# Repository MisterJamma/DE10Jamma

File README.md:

# DE10Jamma

JAMMA/NeoGeo MVS audio, video & control IO for DE10-Nano.

[https://github.com/MisterJamma/DE10Jamma](https://github.com/MisterJamma/DE10Jamma)

Discussion thread: [https://www.atari-forum.com/viewtopic.php?f=120&t=38793](https://www.atari-forum.com/viewtopic.php?f=120&t=38793)

## Description

### Overview
DE10Jamma allows a DE10-Nano board to be connected directly to an arcade cabinet as simply as possible. USB and HDMI serial interfaces are not used, in order to remain as close as possible to the original arcade hardware and avoid unnecessary cost or complexity.

Pull-down resistors on AUDIO_L and AUDIO_R pins allow this board to be detected and coexist with other MiSTer hardware using common rbf files for the cores. See [this commit](https://github.com/MisterJamma/Arcade-GnG_MiSTer/commit/6c7786a7f790a5277f337f6b245e99f6ca4c25ff).

##### Future Developments
Future developments in RTL and software to more fully support DE10Jamma

1. Allow player controls to be used in the OSD.

### Inputs
Inputs are [RC filtered](https://wiki.neogeodev.org/index.php?title=CRE401) to give EMI protection to the FPGA.

No multiplexing, polling or debouncing of the inputs ensures **zero** additional latency & jitter. Cabinet switches are presented to arcade cores exactly as they would be on a real arcade PCB. Arcade cores will include necessary debouncing either in replicated hardware of the original PCB, or in software running on that hardware. When buttons are passed to the ARM host CPU for controlling the UI & selecting arcade cores, the inputs should debounced appropriately in hardware or software.

### Audio Output
2 pole RC filters convert PWM output from DE10-Nano to analog signal. Mono/Stereo jumper JP1 allows stereo signal for MVS wired cabinets, or mono signal for JAMMA wired cabinets. With no jumper fitted, there will be no audio output for the left channel.

2 channel power amplifier drives the speaker loads.

### Video Output
Composite sync is generated by DE10-Nano.

Three 6bit R-2R DACs convert the digital output from DE10-Nano to analog RGB. A single 2R value used in parallel to generate the R value with tighter tolerance. Part-to-part tolerance is typically significantly better than absolute part tolerance, so using a single 2R value for all resistors in the DAC should improve linearity.

No additional latency or incompatibility from HDMI logic and low quality HDMI converters. Resistive DACs are commonly used on arcade PCBs, and allow the original odd resolutions & refresh rates to be supported correctly. Output level is not noticeably lower than a NeoGeo MVS, and well within adjustment range on arcade monitors.

### DC Power Output
DC power output is provided for the DE10-Nano. This should be connected using a short [2.1mm male-male cable](https://www.google.com/search?q=2.1mm+male+to+male&tbm=isch), such as used to connect guitar effects pedals to a power supply.

Arcade power supplies are typically adjustable. DE10-Nano has regulation for lower voltage supplies, and should operate correctly from nominal +5v settings. If +5v rail is adjusted too high, the DE10-Nano's over-voltage protection circuitry will not allow the board to power up.

## Parts List
Qty | Reference(s)         | Value          | Part Number
----|----------------------|----------------|------------
30  | C1, C2, C3, C4, C13, C14, C15, C16, C17, C18, C19, C20, C21, C22, C23, C24, C25, C26, C27, C28, C29, C30, C31, C32, C33, C34, C35, C36, C37, C38 | 10nF | C83170
4   | C5, C6, C7, C11      | 470nF          | C106843
4   | C8, C9, C10, C12     | 1000uF         | C442834
1   | J1, J2, J6           | Long 0.1" pins | C51353
1   | JP1, J3, J4, J5, J11 | 0.1" pins      | C358690
1   | J9                   | 2.5mm JST pins | C160365
1   | J7                   | 0.1" socket    | C35165
1   | J10                  | 2.1mm power    | C319099
1   | R1                   | 100R           | C105577
28  | R2, R3, R34, R35, R36, R37, R38, R39, R40, R41, R42, R43, R44, R45, R60, R61, R62, R63, R64, R65, R66, R67, R68, R69, R70, R71, R72, R73 | 1k | C140870
16  | R4, R100, R101, R102, R103, R104, R105, R106, R107, R108, R109, R110, R111, R112, R113, R114 | 604R | Bourns CAY16-6040F4LF
1   | R8                   | 300k           | C114530
1   | RV1                  | 50k            | C81264
1   | U1                   | TDA7496        | TDA7496
1   | FAN                  | 40mm fan 5/12v | 

###### Notes
   1. Part numbers from [LSSC](https://lcsc.com/) are provided where possible. Values for some components do not match the schematic, and have been adjusted to reduce the number of different components.

   1. J1, J2 and J6 should be inserted into PCB from above, using DE10-Nano to set correct depth. Solder carefully from above & trim to length. Pins should protrude approximately 0.25" from the PCB

   1. J9 is only required for cabinets with 2.5mm pitch JST kick harness connector. It may also be possible to use 0.1" pitch J11 connector with existing kick harness, as the difference in pitch is minimal for a 10way connector.

   1. A 20mm deep fan running on a lower voltage is recommended for reduced noise.

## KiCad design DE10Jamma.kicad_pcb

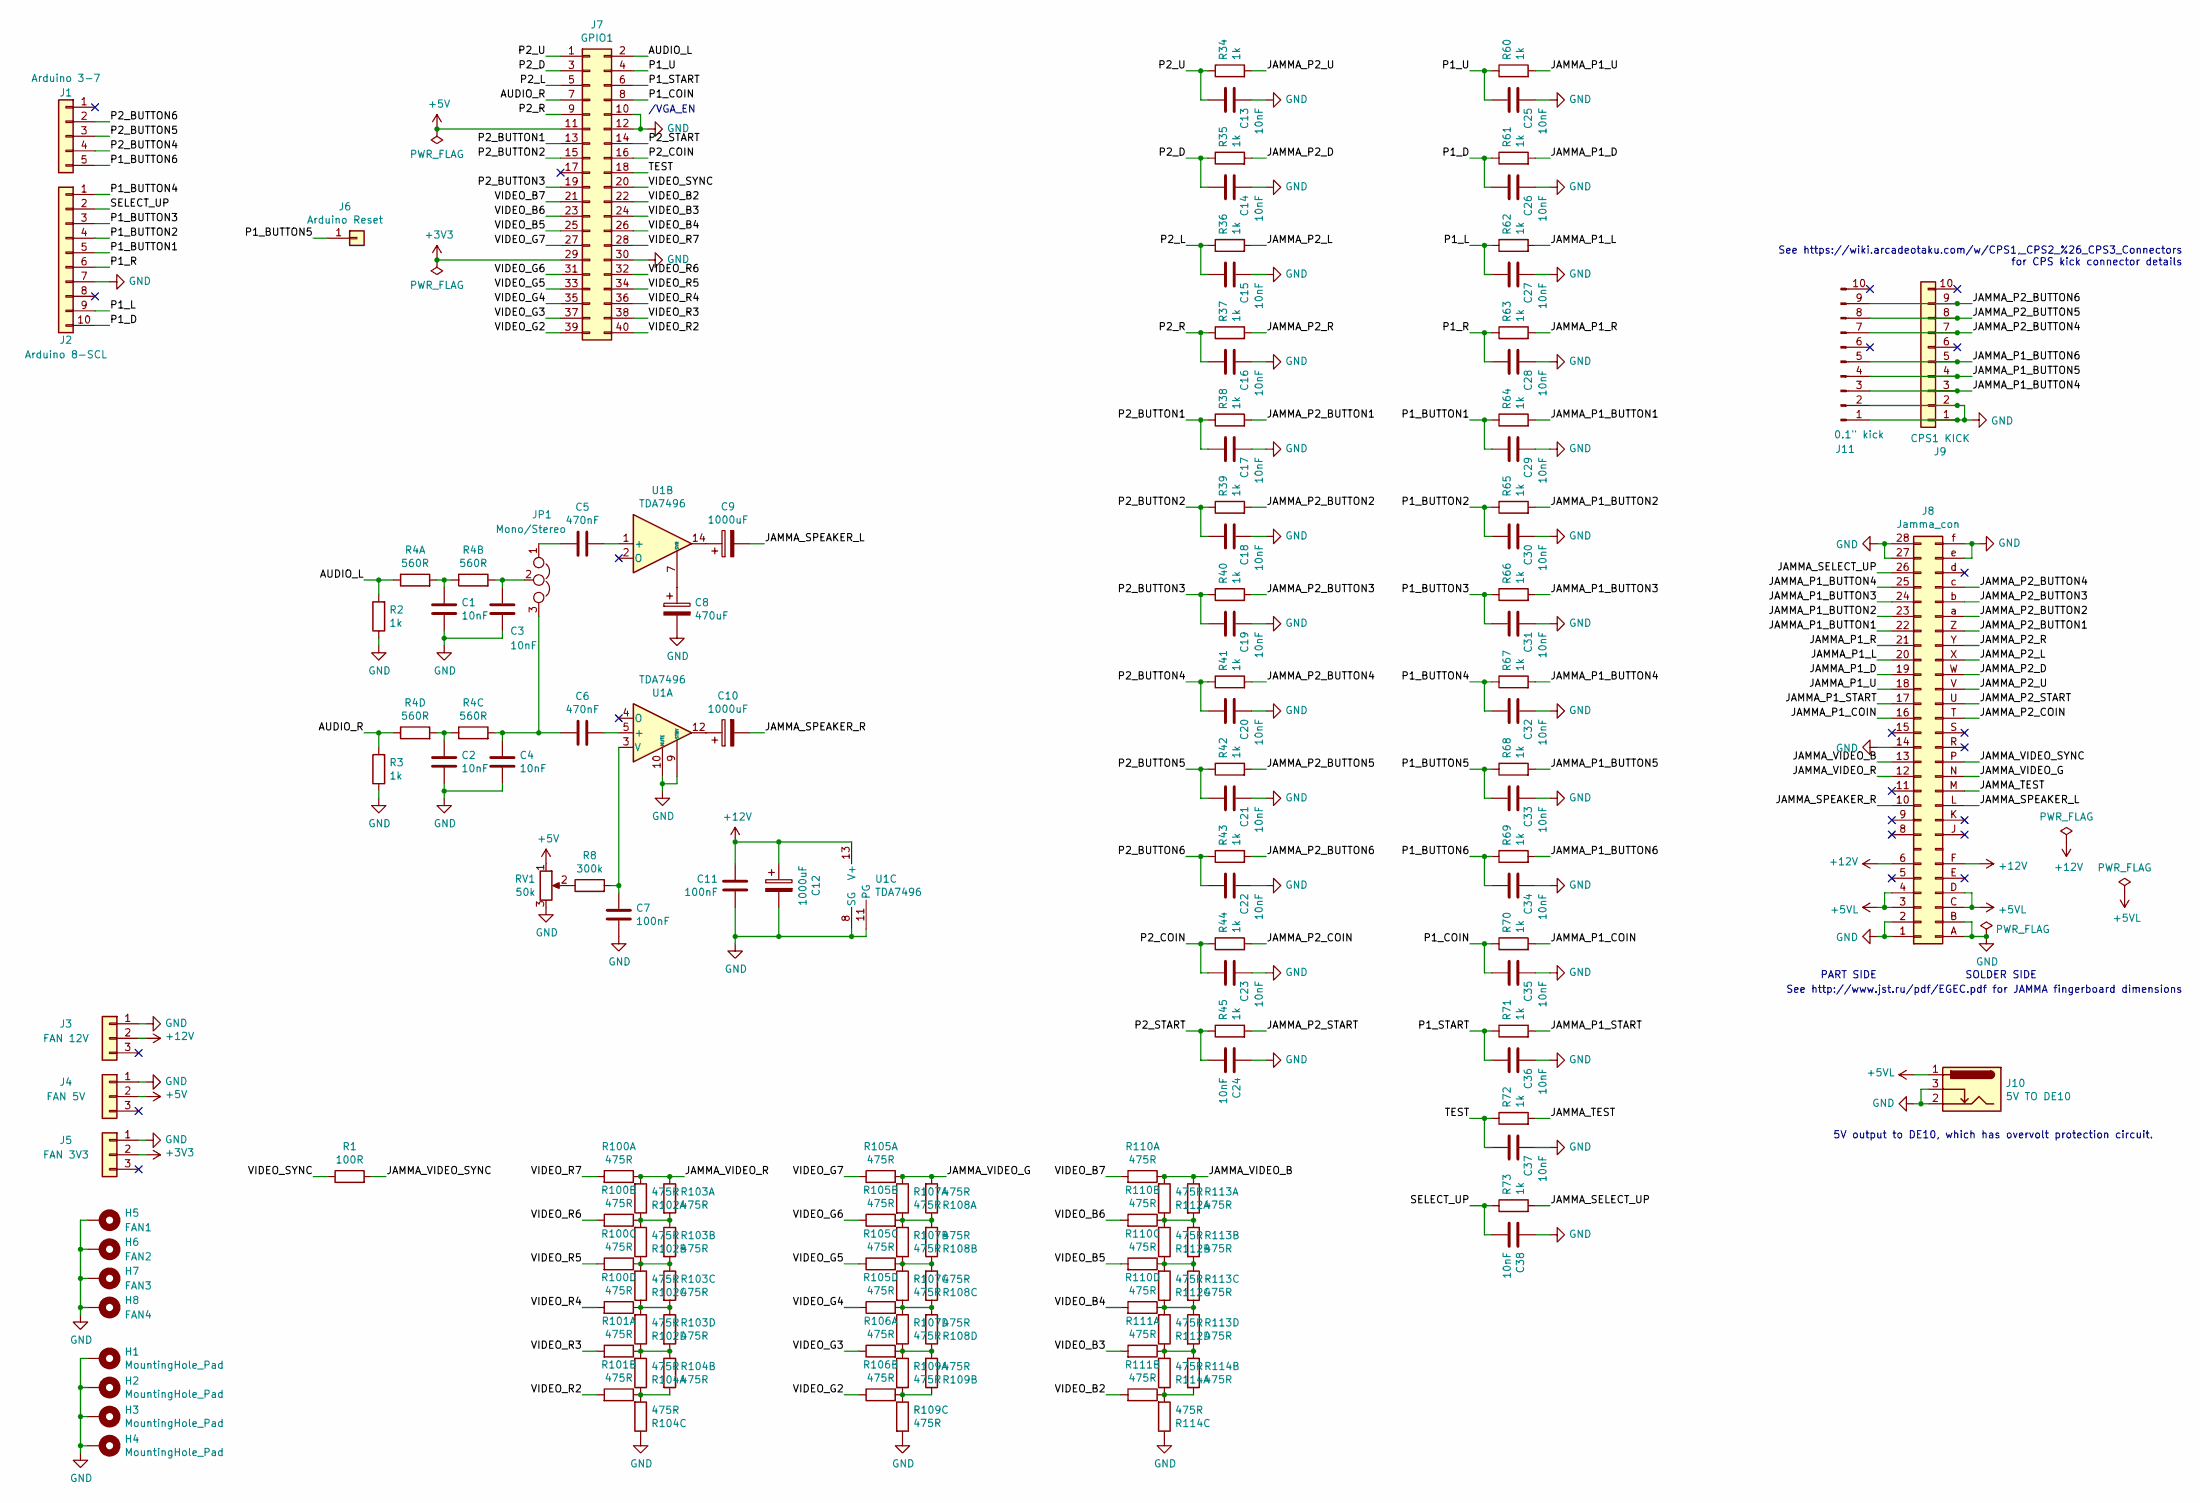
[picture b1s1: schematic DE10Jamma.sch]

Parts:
C1, C2, C3, C4, C13, C14, C15, C16, C17, C18, C19, C20, C21, C22, C23, C24, C25, C26, C27, C28, C29, C30, C31, C32, C33, C34, C35, C36, C37, C38: 10nF; C_0805_2012Metric
C5, C6: 470nF; C_0805_2012Metric
C7, C11: 100nF; C_0805_2012Metric
C8: 470uF; CP_Radial_D10.0mm_P5.00mm
C9, C10, C12: 1000uF; CP_Radial_D10.0mm_P5.00mm
H1, H2, H3, H4: MountingHole_Pad; MountingHole_3mm_Pad_Via
H5: FAN1; MountingHole_3mm
H6: FAN2; MountingHole_3mm
H7: FAN3; MountingHole_3mm
H8: FAN4; MountingHole_3mm
J1: Arduino 3-7; PinHeader_1x05_P2.54mm_Vertical
J2: Arduino 8-SCL; PinHeader_1x10_P2.54mm_Vertical
J3: FAN 12V; PinHeader_1x03_P2.54mm_Vertical
J4: FAN 5V; PinHeader_1x03_P2.54mm_Vertical
J5: FAN 3V3; PinHeader_1x03_P2.54mm_Vertical
J6: Arduino Reset; PinHeader_1x01_P2.54mm_Vertical
J7: GPIO1; PinSocket_2x20_P2.54mm_Vertical
J8: Jamma_con; JAMMA-56
J9: CPS1 KICK; JST_EH_B10B-EH-A_1x10_P2.50mm_Vertical
J10: 5V TO DE10; BarrelJack_Horizontal
J11: 0.1\" kick; PinHeader_1x10_P2.54mm_Vertical
JP1: Mono/Stereo; PinHeader_1x03_P2.54mm_Vertical
R1: 100R; C_0805_2012Metric
R2, R3, R34, R35, R36, R37, R38, R39, R40, R41, R42, R43, R44, R45, R60, R61, R62, R63, R64, R65, R66, R67, R68, R69, R70, R71, R72, R73: 1k; C_0805_2012Metric
R4: 560R; R_Array_Convex_4x0603
R8: 300k; C_0805_2012Metric
R100, R101, R102, R103, R104, R105, R106, R107, R108, R109, R110, R111, R112, R113, R114: 475R; R_Array_Convex_4x0603
RV1: 50k; Potentiometer_Vishay_T73YP_Vertical
U1: TDA7496; TO-220-15_P2.54x2.54mm_StaggerOdd_Lead4.58mm_Vertical

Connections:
+3V3: J5.2, J7.29
+5V: J4.2, J7.11, RV1.1
+5VL: J8.3 (+5V), J8.4 (+5V), J8.C (+5V), J8.D (+5V), J10.1
+12V: C11.1, C12.1, J3.2, J8.6 (+12V), J8.F (+12V), U1.13 (V+)
/AUDIO_L: J7.2, R2.2, R4.8
/AUDIO_R: J7.7, R3.2, R4.5
/JAMMA_P1_BUTTON1: J8.22 (P1_BUTTON_1), R64.2
/JAMMA_P1_BUTTON2: J8.23 (P1_BUTTON_2), R65.2
/JAMMA_P1_BUTTON3: J8.24 (P1_BUTTON_3), R66.2
/JAMMA_P1_BUTTON4: J8.25 (P1_BUTTON_4), J9.3, J11.3, R67.2
/JAMMA_P1_BUTTON5: J9.4, J11.4, R68.2
/JAMMA_P1_BUTTON6: J9.5, J11.5, R69.2
/JAMMA_P1_COIN: J8.16 (COIN_1), R70.2
/JAMMA_P1_D: J8.19 (P1_DOWN), R61.2
/JAMMA_P1_L: J8.20 (P1_LEFT), R62.2
/JAMMA_P1_R: J8.21 (P1_RIGHT), R63.2
/JAMMA_P1_START: J8.17 (START_1), R71.2
/JAMMA_P1_U: J8.18 (P1_UP), R60.2
/JAMMA_P2_BUTTON1: J8.Z (P2_BUTTON_1), R38.2
/JAMMA_P2_BUTTON2: J8.a (P2_BUTTON_2), R39.2
/JAMMA_P2_BUTTON3: J8.b (P2_BUTTON_3), R40.2
/JAMMA_P2_BUTTON4: J8.c (P2_BUTTON_4), J9.7, J11.7, R41.2
/JAMMA_P2_BUTTON5: J9.8, J11.8, R42.2
/JAMMA_P2_BUTTON6: J9.9, J11.9, R43.2
/JAMMA_P2_COIN: J8.T (COIN_2), R44.2
/JAMMA_P2_D: J8.W (P2_DOWN), R35.2
/JAMMA_P2_L: J8.X (P2_LEFT), R36.2
/JAMMA_P2_R: J8.Y (P2_RIGHT), R37.2
/JAMMA_P2_START: J8.U (START_2), R45.2
/JAMMA_P2_U: J8.V (P2_UP), R34.2
/JAMMA_SELECT_UP: J8.26 (SELECT_UP), R73.2
/JAMMA_SPEAKER_L: C9.2, J8.L (SPEAKER-)
/JAMMA_SPEAKER_R: C10.2, J8.10 (SPEAKER+)
/JAMMA_TEST: J8.M (TEST), R72.2
/JAMMA_VIDEO_B: J8.13 (VIDEO_BLUE), R110.8, R112.1, R113.8
/JAMMA_VIDEO_G: J8.N (VIDEO_GREEN), R105.1, R107.8, R108.1
/JAMMA_VIDEO_R: J8.12 (VIDEO_RED), R100.8, R102.1, R103.8
/JAMMA_VIDEO_SYNC: J8.P (VIDEO_SYNC), R1.2
/P1_BUTTON1: C29.2, J2.5, R64.1
/P1_BUTTON2: C30.2, J2.4, R65.1
/P1_BUTTON3: C31.2, J2.3, R66.1
/P1_BUTTON4: C32.2, J2.1, R67.1
/P1_BUTTON5: C33.2, J6.1, R68.1
/P1_BUTTON6: C34.2, J1.5, R69.1
/P1_COIN: C35.2, J7.8, R70.1
/P1_D: C26.2, J2.10, R61.1
/P1_L: C27.2, J2.9, R62.1
/P1_R: C28.2, J2.6, R63.1
/P1_START: C36.2, J7.6, R71.1
/P1_U: C25.2, J7.4, R60.1
/P2_BUTTON1: C17.2, J7.13, R38.1
/P2_BUTTON2: C18.2, J7.15, R39.1
/P2_BUTTON3: C19.2, J7.19, R40.1
/P2_BUTTON4: C20.2, J1.4, R41.1
/P2_BUTTON5: C21.2, J1.3, R42.1
/P2_BUTTON6: C22.2, J1.2, R43.1
/P2_COIN: C23.2, J7.16, R44.1
/P2_D: C14.2, J7.3, R35.1
/P2_L: C15.2, J7.5, R36.1
/P2_R: C16.2, J7.9, R37.1
/P2_START: C24.2, J7.14, R45.1
/P2_U: C13.2, J7.1, R34.1
/SELECT_UP: C38.2, J2.2, R73.1
/TEST: C37.2, J7.18, R72.1
/VIDEO_B2: J7.22, R111.2
/VIDEO_B3: J7.24, R111.1
/VIDEO_B4: J7.26, R110.4
/VIDEO_B5: J7.25, R110.3
/VIDEO_B6: J7.23, R110.2
/VIDEO_B7: J7.21, R110.1
/VIDEO_G2: J7.39, R106.7
/VIDEO_G3: J7.37, R106.8
/VIDEO_G4: J7.35, R105.5
/VIDEO_G5: J7.33, R105.6
/VIDEO_G6: J7.31, R105.7
/VIDEO_G7: J7.27, R105.8
/VIDEO_R2: J7.40, R101.2
/VIDEO_R3: J7.38, R101.1
/VIDEO_R4: J7.36, R100.4
/VIDEO_R5: J7.34, R100.3
/VIDEO_R6: J7.32, R100.2
/VIDEO_R7: J7.28, R100.1
/VIDEO_SYNC: J7.20, R1.1
GND: C1.2, C2.2, C3.2, C4.2, C7.2, C8.2, C11.2, C12.2, C13.1, C14.1, C15.1, C16.1, C17.1, C18.1, C19.1, C20.1, C21.1, C22.1, C23.1, C24.1, C25.1, C26.1, C27.1, C28.1, C29.1, C30.1, C31.1, C32.1, C33.1, C34.1, C35.1, C36.1, C37.1, C38.1, H1.1, H2.1, H3.1, H4.1, H5.1, H6.1, H7.1, H8.1, J2.7, J3.1, J4.1, J5.1, J7.10, J7.12, J7.30, J8.1 (GND), J8.2 (GND), J8.14 (VIDEO_GND), J8.27 (GND), J8.28 (GND), J8.A (GND), J8.B (GND), J8.e (GND), J8.f (GND), J9.1, J9.2, J10.2, J10.3, J11.1, J11.2, R2.1, R3.1, R104.6, R109.3, R114.6, RV1.3, U1.8 (SG), U1.9 (STBY), U1.10 (MUTE), U1.11 (PG), U1.15 (PG)
unnamed: C1.1, R4.1, R4.7
unnamed: C2.1, R4.4, R4.6
unnamed: C3.1, JP1.2, R4.2
unnamed: C4.1, C6.1, JP1.3, R4.3
unnamed: C5.1, JP1.1
unnamed: C5.2, U1.1 (+)
unnamed: C6.2, U1.5 (+)
unnamed: C7.1, R8.2, U1.3 (V)
unnamed: C8.1, U1.7 (SVR)
unnamed: C9.1, U1.14
unnamed: C10.1, U1.12
unnamed: R8.1, RV1.2
unnamed: R100.5, R102.4, R102.6, R103.3, R103.5
unnamed: R100.6, R102.3, R102.7, R103.2, R103.6
unnamed: R100.7, R102.2, R102.8, R103.1, R103.7
unnamed: R101.7, R104.2, R104.3, R104.8
unnamed: R101.8, R102.5, R103.4, R104.1, R104.7
unnamed: R105.2, R107.1, R107.7, R108.2, R108.8
unnamed: R105.3, R107.2, R107.6, R108.3, R108.7
unnamed: R105.4, R107.3, R107.5, R108.4, R108.6
unnamed: R106.1, R107.4, R108.5, R109.2, R109.8
unnamed: R106.2, R109.1, R109.6, R109.7
unnamed: R110.5, R112.4, R112.6, R113.3, R113.5
unnamed: R110.6, R112.3, R112.7, R113.2, R113.6
unnamed: R110.7, R112.2, R112.8, R113.1, R113.7
unnamed: R111.7, R114.2, R114.3, R114.8
unnamed: R111.8, R112.5, R113.4, R114.1, R114.7

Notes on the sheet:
PART SIDE
SOLDER SIDE
/VGA_EN
5V output to DE10, which has overvolt protection circuit.
See http://www.jst.ru/pdf/EGEC.pdf for JAMMA fingerboard dimensions
See https://wiki.arcadeotaku.com/w/CPS1,_CPS2_%26_CPS3_Connectors for CPS kick connector details

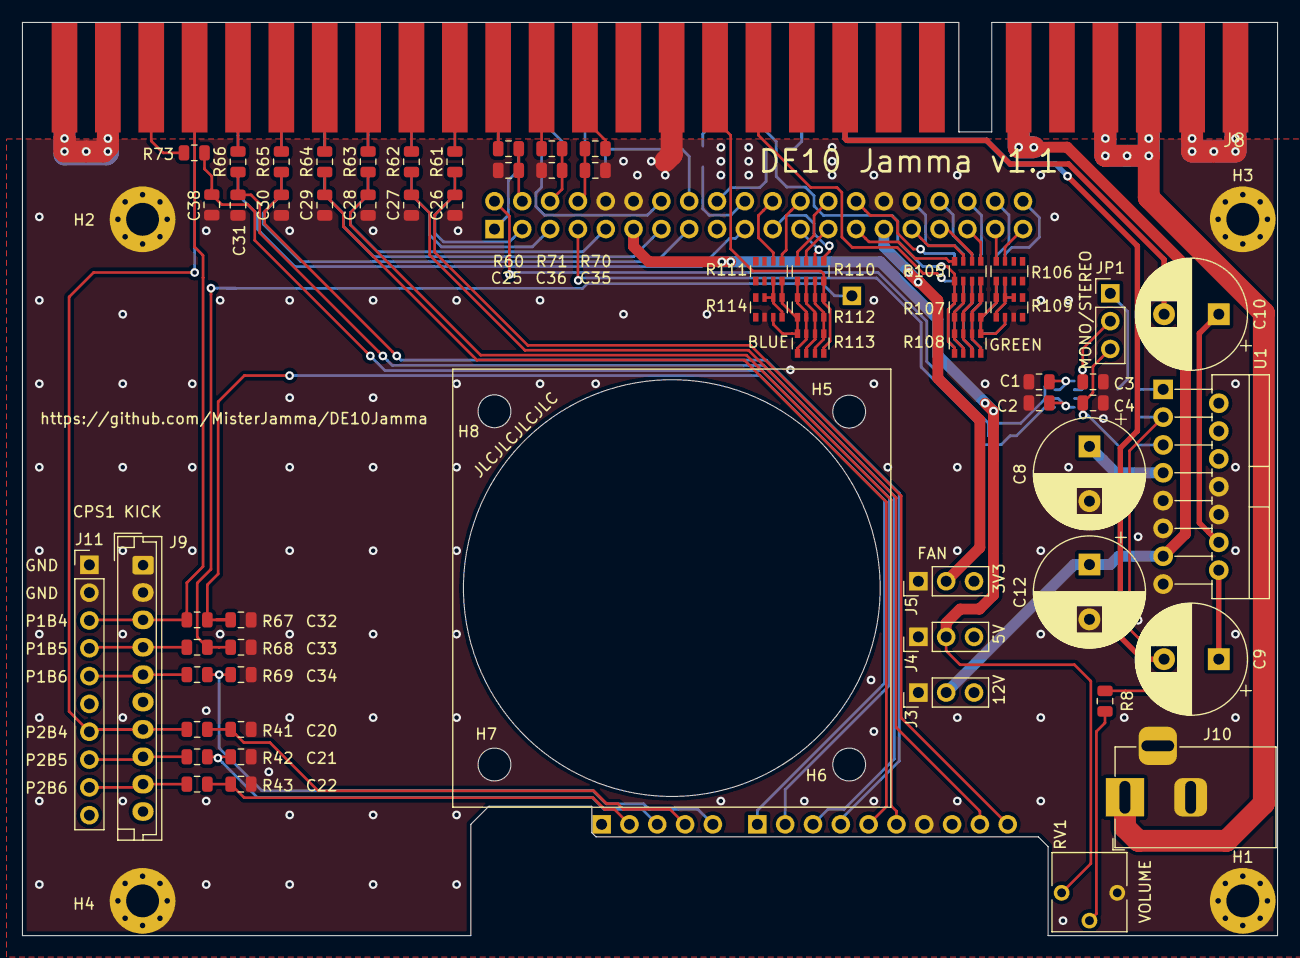
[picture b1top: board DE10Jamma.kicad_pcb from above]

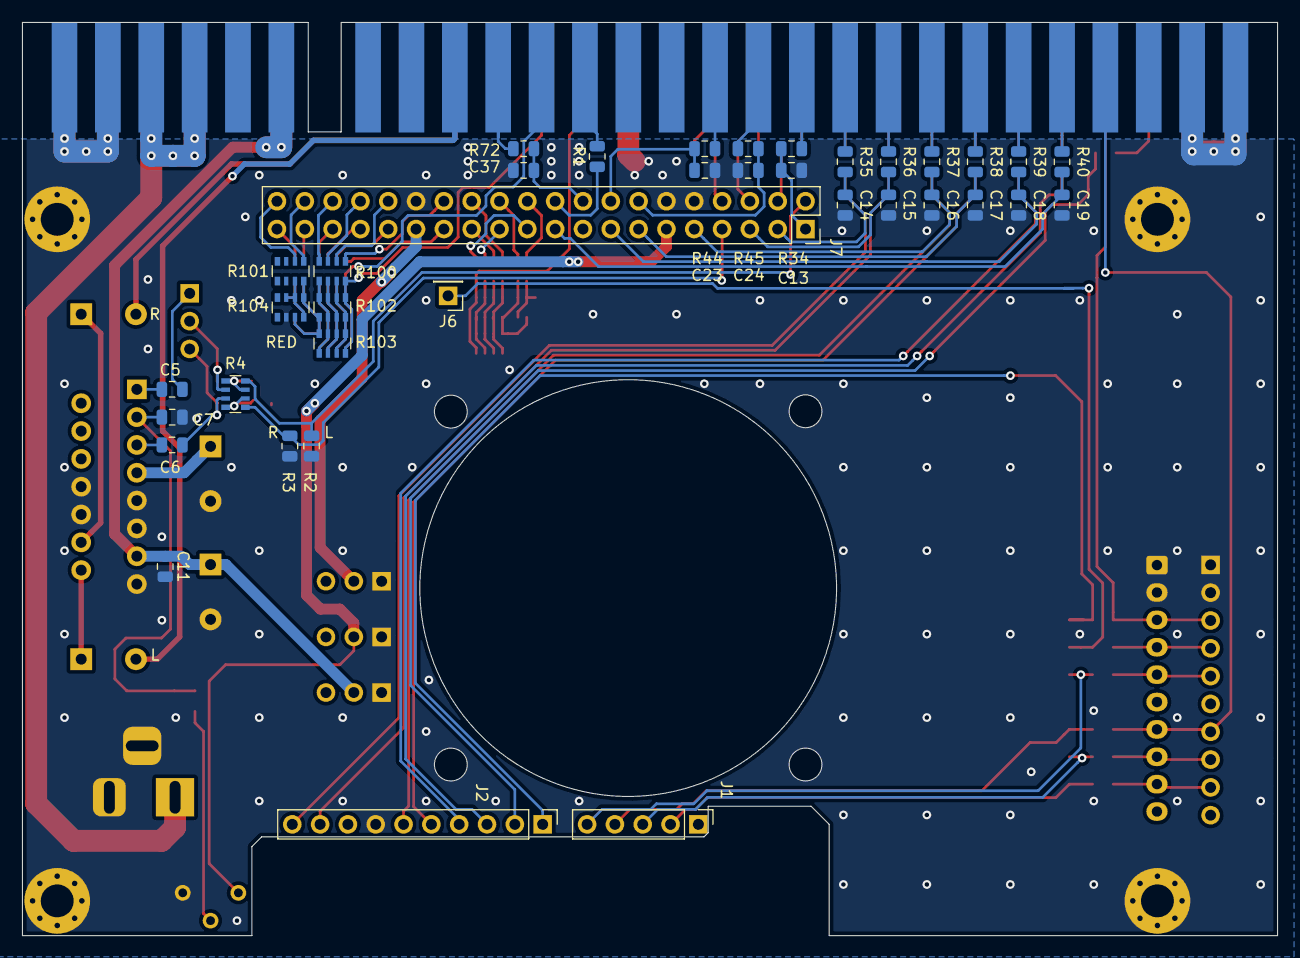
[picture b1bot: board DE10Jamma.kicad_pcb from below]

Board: 2 copper layers, 114.6 x 83.4 mm, 106 parts (37 on the bottom side), 111 nets.

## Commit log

2020-05-03 pdf of schematic
2020-07-05 clean before sending to manufacture
2020-07-05 Add mono/stereo jumper. Remove out of date pdf
2020-08-02 Use smaller footprint for r-packs. Rework mono/stereo jumper to avoid potential DC path issues if inputs have DC offset. General routing & silk screen cleanup.
2020-08-02 add jpg to readme
2020-08-15 Route wire into JAMMA _VIDEO_G pad properly
2020-08-16 Update pic & status of IO Board compatibility
2020-08-18 Add link to forum thread
